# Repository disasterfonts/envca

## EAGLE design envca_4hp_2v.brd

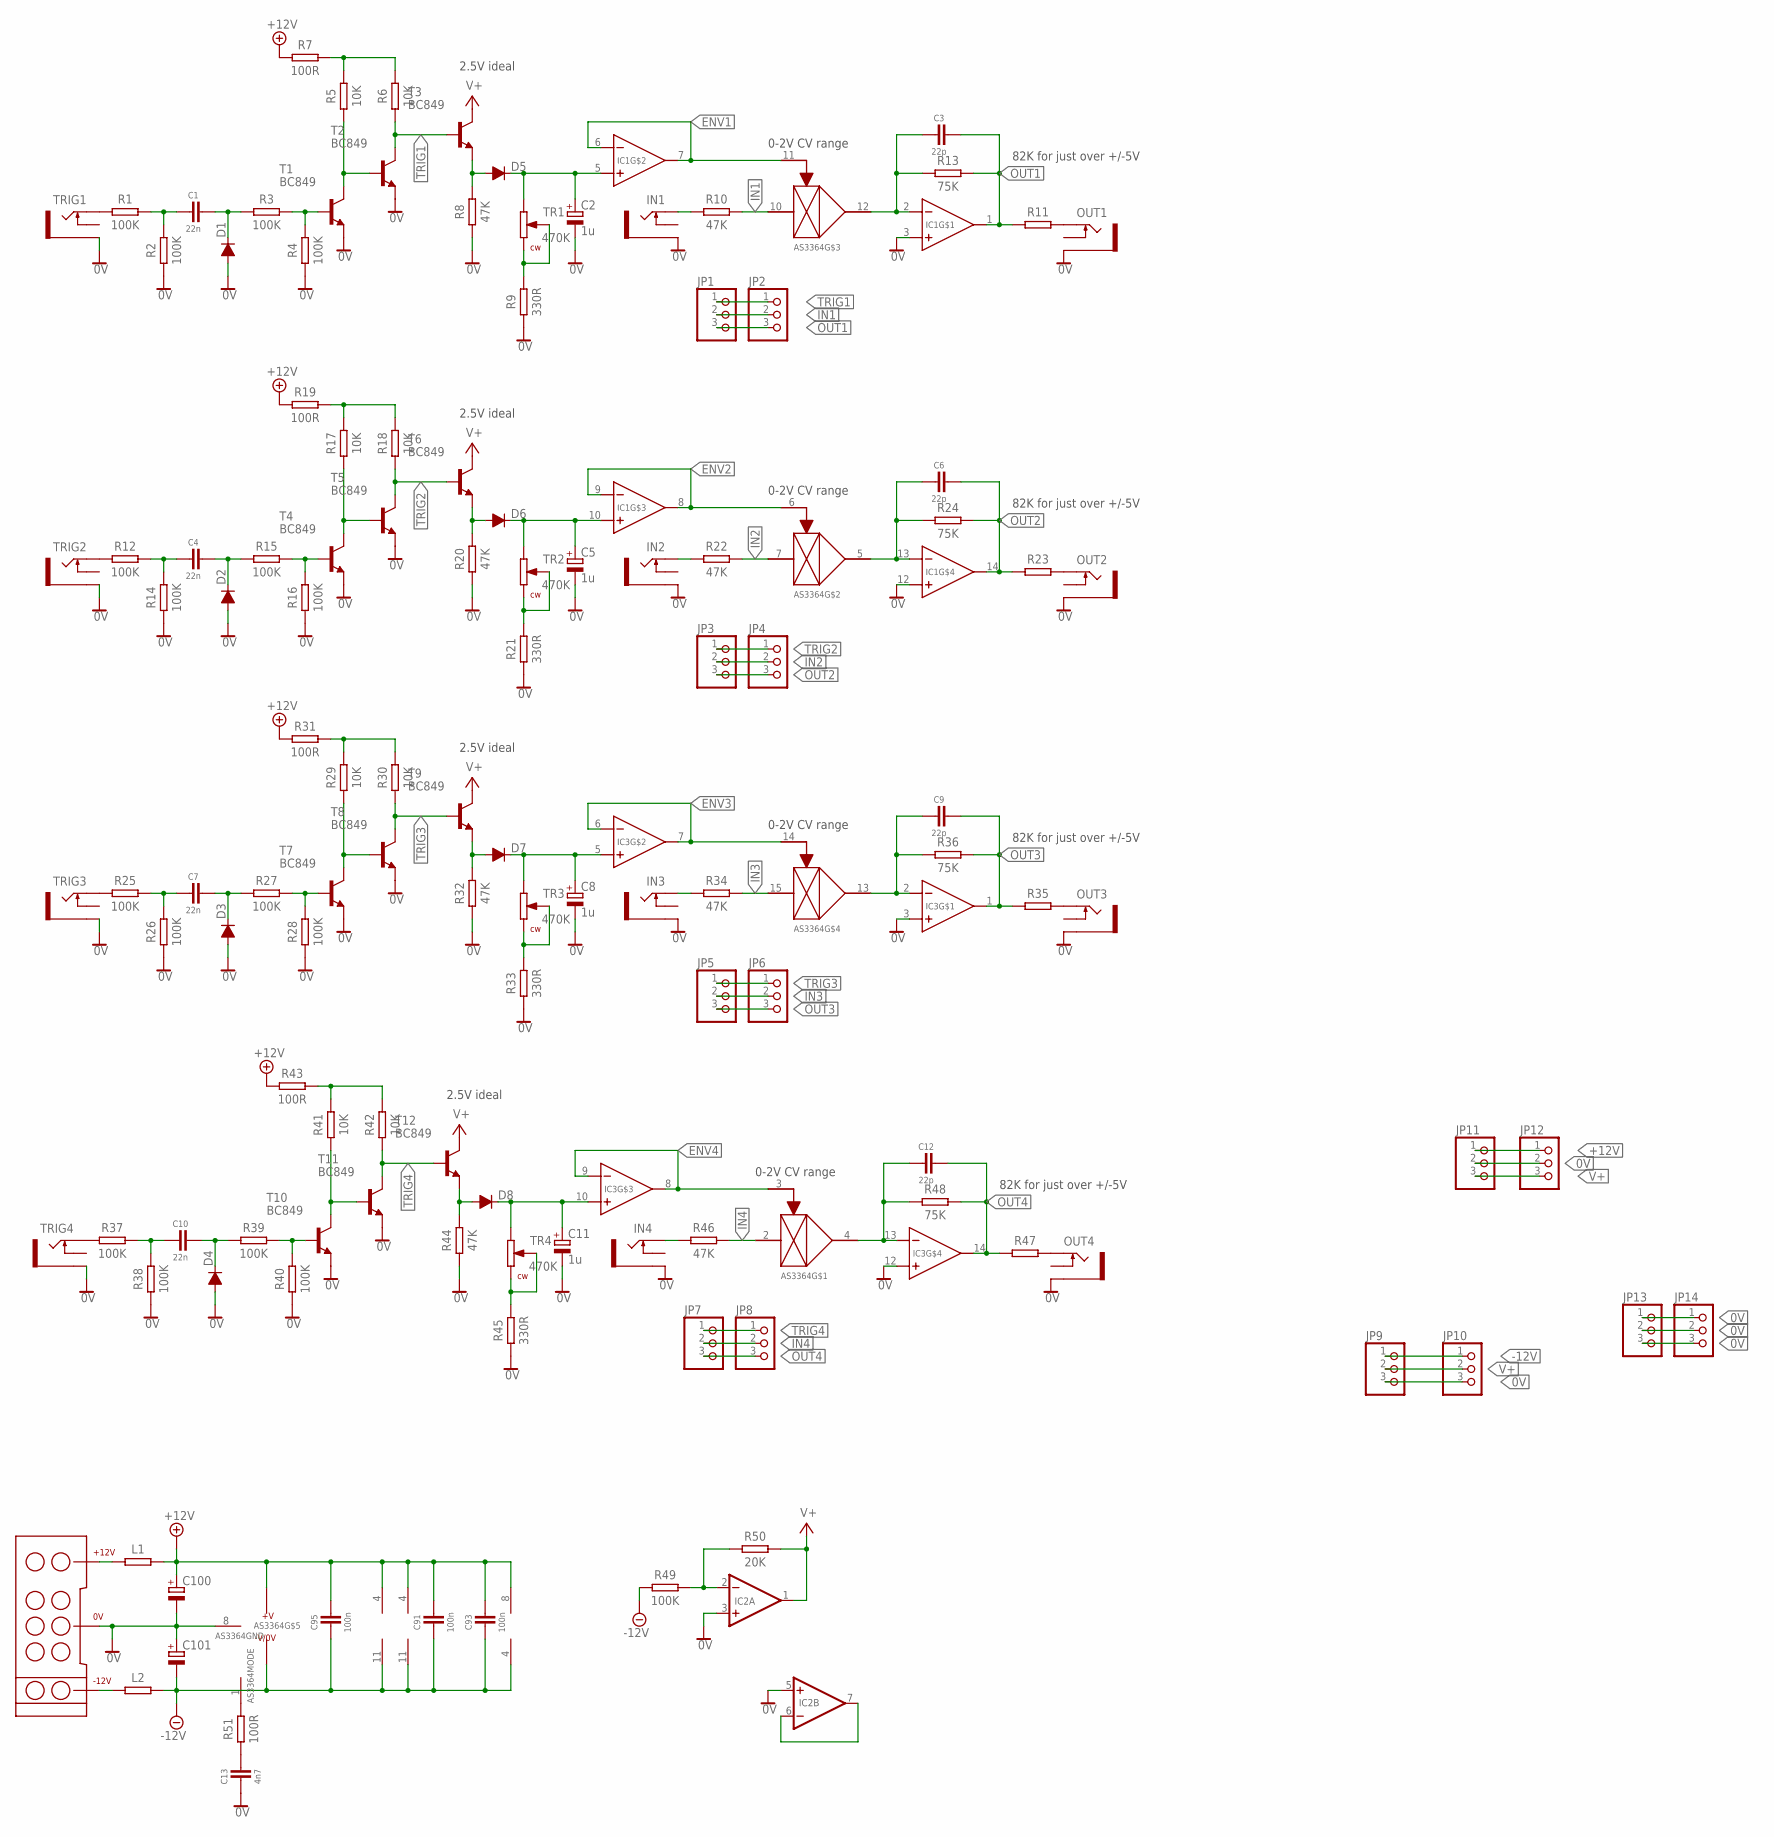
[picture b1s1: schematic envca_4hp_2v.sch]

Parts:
AS3364: AS2164_SMD; SO16
C1, C4, C7, C10: 22n; C0805
C2, C5, C8, C11: 1u; E2,5-6
C3, C6, C9, C12: 22p; C0805
C13: 4n7; C0805
C91, C93, C95: 100n; C0805
C100, C101: CPOL-EUE2.5-6; E2,5-6
D1, D2, D3, D4, D5, D6, D7, D8: DIODE-SOD123; SOD123
IC1, IC3: TL074_SO14; SO14
IC2: TL072_SMDD; SO08
IN1, IN2, IN3, IN4: THONKICONN
JP1, JP2, JP3, JP4, JP5, JP6, JP7, JP8, JP9, JP10, JP11, JP12, JP13, JP14: PINHD-1X3; 1X03
L1, L2: RESISTOR_0805; R0805
OUT1, OUT2, OUT3, OUT4: THONKICONN
R1, R2, R3, R4, R12, R14, R15, R16, R25, R26, R27, R28, R37, R38, R39, R40, R49: 100K; R0805
R5, R6, R17, R18, R29, R30, R41, R42: 10K; R0805
R7, R19, R31, R43, R51: 100R; R0805
R8, R10, R20, R22, R32, R34, R44, R46: 47K; R0805
R9, R21, R33, R45: 330R; R0805
R11, R23, R35, R47: RESISTOR_0805; R0805
R13, R24, R36, R48: 75K; R0805
R50: 20K; R0805
T1, T2, T3, T4, T5, T6, T7, T8, T9, T10, T11, T12: BC849; SOT23
TR1, TR2, TR3, TR4: 470K; TRIMMER3362
TRIG1, TRIG2, TRIG3, TRIG4: THONKICONN
U$1: EURO_POWER

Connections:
0V: AS3364.8, C2.-, C5.-, C8.-, C11.-, C13.1, C100.-, C101.+, D1.A, D2.A, D3.A, D4.A, IC1.3 (+), IC1.12 (+), IC2.3 (+IN), IC2.5 (+IN), IC3.3 (+), IC3.12 (+), IN1.P$3_SLEEVE (SLEEVE), IN2.P$3_SLEEVE (SLEEVE), IN3.P$3_SLEEVE (SLEEVE), IN4.P$3_SLEEVE (SLEEVE), JP9.3, JP10.3, JP11.2, JP12.2, JP13.1, JP13.2, JP13.3, JP14.1, JP14.2, JP14.3, OUT1.P$3_SLEEVE (SLEEVE), OUT2.P$3_SLEEVE (SLEEVE), OUT3.P$3_SLEEVE (SLEEVE), OUT4.P$3_SLEEVE (SLEEVE), R2.1, R4.1, R8.1, R9.1, R14.1, R16.1, R20.1, R21.1, R26.1, R28.1, R32.1, R33.1, R38.1, R40.1, R44.1, R45.1, T1.2 (E), T2.2 (E), T4.2 (E), T5.2 (E), T7.2 (E), T8.2 (E), T10.2 (E), T11.2 (E), TRIG1.P$3_SLEEVE (SLEEVE), TRIG2.P$3_SLEEVE (SLEEVE), TRIG3.P$3_SLEEVE (SLEEVE), TRIG4.P$3_SLEEVE (SLEEVE), U$1.3 (0V), U$1.4 (0V), U$1.5 (0V), U$1.6 (0V), U$1.7 (0V), U$1.8 (0V)
+12V: AS3364.16 (VDD), C91.2, C93.2, C95.2, C100.+, IC1.4 (V+), IC2.8 (V+), IC3.4 (V+), JP11.1, JP12.1, L1.2, R7.1, R19.1, R31.1, R43.1
-12V: AS3364.9 (VSS), C91.1, C93.1, C95.1, C101.-, IC1.11 (V-), IC2.4 (V-), IC3.11 (V-), JP9.1, JP10.1, L2.2, R49.1
ENV1: AS3364.11 (VC), IC1.6 (-), IC1.7 (OUT)
ENV2: AS3364.6 (VC), IC1.8 (OUT), IC1.9 (-)
ENV3: AS3364.14 (VC), IC3.6 (-), IC3.7 (OUT)
ENV4: AS3364.3 (VC), IC3.8 (OUT), IC3.9 (-)
IN1: AS3364.10 (IN), JP1.2, JP2.2, R10.2
IN2: AS3364.7 (IN), JP3.2, JP4.2, R22.2
IN3: AS3364.15 (IN), JP5.2, JP6.2, R34.2
IN4: AS3364.2 (IN), JP7.2, JP8.2, R46.2
unnamed: L1.1, U$1.9 (+12V), U$1.10 (+12V)
unnamed: L2.1, U$1.1 (-12V), U$1.2 (-12V)
unnamed: IN1.P$1_TIP (TIP), R10.1
unnamed: C2.+, D5.C, IC1.5 (+), TR1.P$1
unnamed: R5.1, T1.3 (C), T2.1 (B)
unnamed: C1.2, D1.C, R3.1
unnamed: R3.2, R4.2, T1.1 (B)
unnamed: C1.1, R1.2, R2.2
unnamed: R5.2, R6.2, R7.2
unnamed: R9.2, TR1.P$2A, TR1.P$2B, TR1.P$3
unnamed: OUT1.P$1_TIP (TIP), R11.2
unnamed: R1.1, TRIG1.P$1_TIP (TIP)
unnamed: C5.+, D6.C, IC1.10 (+), TR2.P$1
unnamed: AS3364.12 (OUT), C3.1, IC1.2 (-), R13.1
unnamed: R17.1, T4.3 (C), T5.1 (B)
unnamed: C8.+, D7.C, IC3.5 (+), TR3.P$1
unnamed: C4.2, D2.C, R15.1
unnamed: R15.2, R16.2, T4.1 (B)
unnamed: C4.1, R12.2, R14.2
unnamed: R17.2, R18.2, R19.2
unnamed: R21.2, TR2.P$2A, TR2.P$2B, TR2.P$3
unnamed: R12.1, TRIG2.P$1_TIP (TIP)
unnamed: IN2.P$1_TIP (TIP), R22.1
unnamed: OUT2.P$1_TIP (TIP), R23.2
unnamed: AS3364.5 (OUT), C6.1, IC1.13 (-), R24.1
unnamed: R29.1, T7.3 (C), T8.1 (B)
unnamed: C7.2, D3.C, R27.1
unnamed: R27.2, R28.2, T7.1 (B)
unnamed: C7.1, R25.2, R26.2
unnamed: R29.2, R30.2, R31.2
unnamed: R33.2, TR3.P$2A, TR3.P$2B, TR3.P$3
unnamed: R25.1, TRIG3.P$1_TIP (TIP)
unnamed: IN3.P$1_TIP (TIP), R34.1
unnamed: OUT3.P$1_TIP (TIP), R35.2
unnamed: AS3364.13 (OUT), C9.1, IC3.2 (-), R36.1
unnamed: C11.+, D8.C, IC3.10 (+), TR4.P$1
unnamed: R41.1, T10.3 (C), T11.1 (B)
unnamed: C10.2, D4.C, R39.1
unnamed: R39.2, R40.2, T10.1 (B)
unnamed: C10.1, R37.2, R38.2
unnamed: R41.2, R42.2, R43.2
unnamed: R45.2, TR4.P$2A, TR4.P$2B, TR4.P$3
unnamed: R37.1, TRIG4.P$1_TIP (TIP)
unnamed: IN4.P$1_TIP (TIP), R46.1
unnamed: OUT4.P$1_TIP (TIP), R47.2
unnamed: AS3364.4 (OUT), C12.1, IC3.13 (-), R48.1
unnamed: IC2.2 (-IN), R49.2, R50.1
unnamed: IC2.6 (-IN), IC2.7 (OUT)
unnamed: D5.A, R8.2, T3.2 (E)
unnamed: D6.A, R20.2, T6.2 (E)
unnamed: D7.A, R32.2, T9.2 (E)
unnamed: D8.A, R44.2, T12.2 (E)
unnamed: AS3364.1, R51.2
unnamed: C13.2, R51.1
OUT1: C3.2, IC1.1 (OUT), JP1.3, JP2.3, R11.1, R13.2
OUT2: C6.2, IC1.14 (OUT), JP3.3, JP4.3, R23.1, R24.2
OUT3: C9.2, IC3.1 (OUT), JP5.3, JP6.3, R35.1, R36.2
OUT4: C12.2, IC3.14 (OUT), JP7.3, JP8.3, R47.1, R48.2
TRIG1: JP1.1, JP2.1, R6.1, T2.3 (C), T3.1 (B)
TRIG2: JP3.1, JP4.1, R18.1, T5.3 (C), T6.1 (B)
TRIG3: JP5.1, JP6.1, R30.1, T8.3 (C), T9.1 (B)
TRIG4: JP7.1, JP8.1, R42.1, T11.3 (C), T12.1 (B)
V+: IC2.1 (OUT), JP9.2, JP10.2, JP11.3, JP12.3, R50.2, T3.3 (C), T6.3 (C), T9.3 (C), T12.3 (C)

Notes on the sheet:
0-2V CV range
2.5V ideal
82K for just over +/-5V

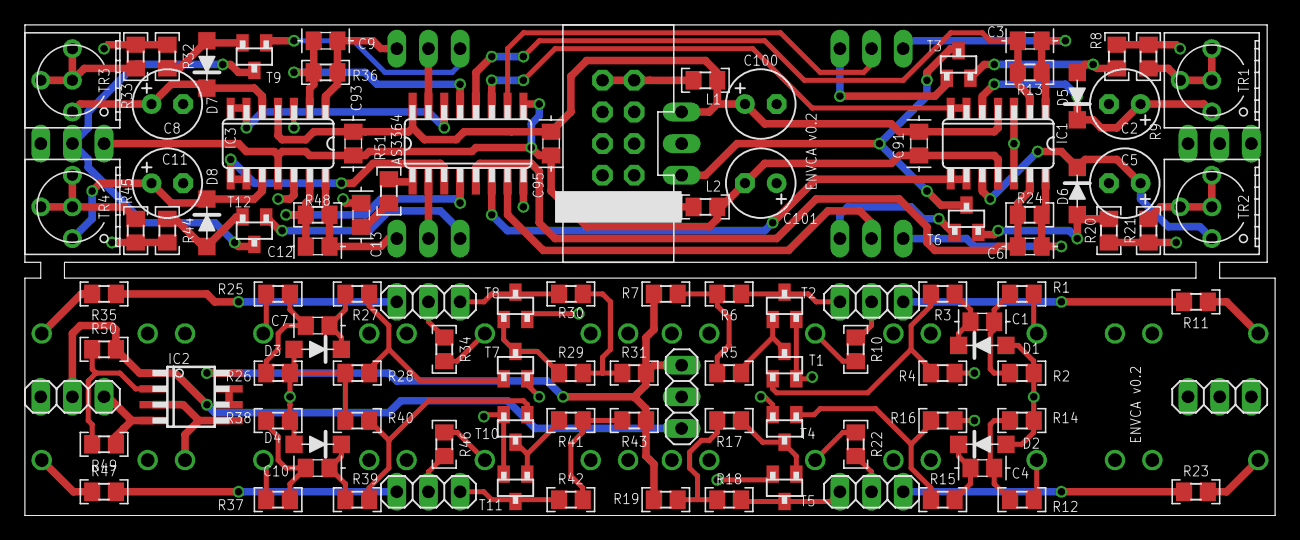
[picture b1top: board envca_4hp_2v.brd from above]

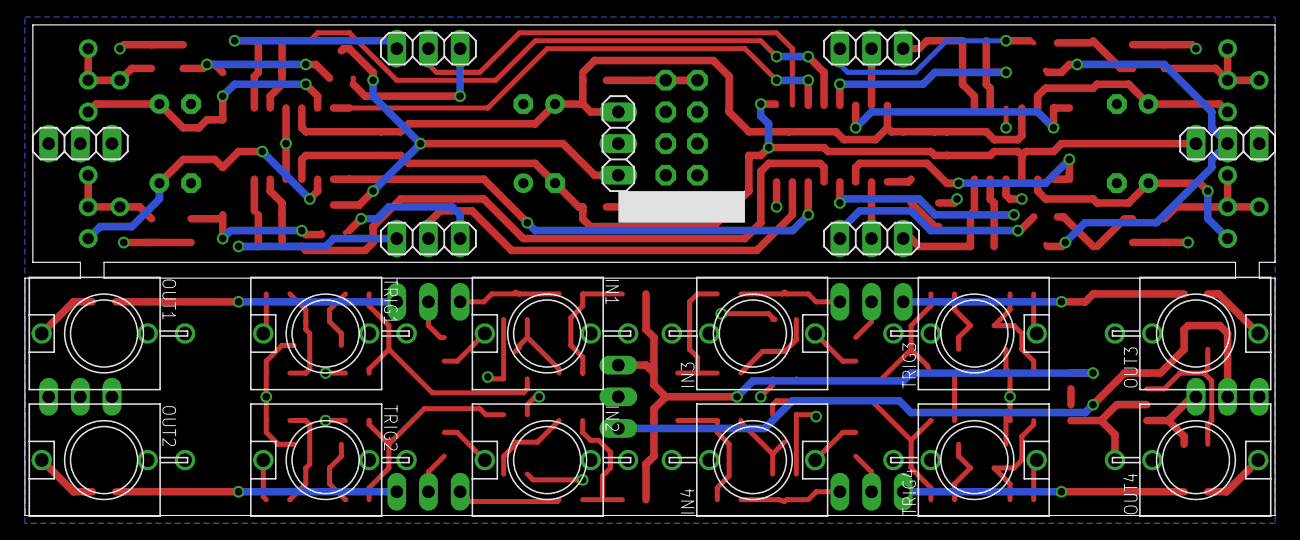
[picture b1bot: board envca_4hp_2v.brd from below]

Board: 2 copper layers, 100.3 x 39.4 mm, 126 parts (19 on the bottom side), 74 nets.

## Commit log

2025-07-02 init commit
2025-07-06 added .gitattributes to stop gerbers getting marked as typescript
